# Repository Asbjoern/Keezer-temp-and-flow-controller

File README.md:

# Keezer temp and flow controller
 Beer fridge controller with stock counting

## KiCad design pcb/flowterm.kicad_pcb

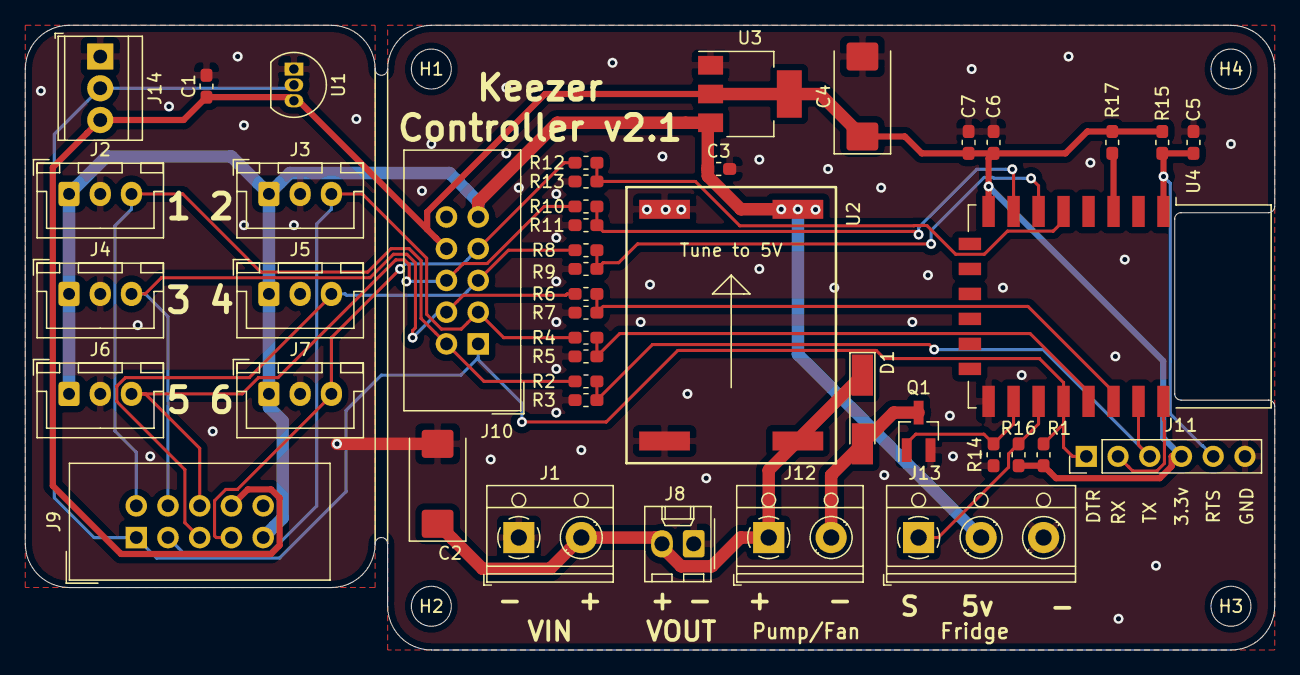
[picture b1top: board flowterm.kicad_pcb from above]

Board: 2 copper layers, 100.0 x 50.0 mm, 48 parts (0 on the bottom side), 23 nets.

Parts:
C1, C5, C7: 100n; C_0603_1608Metric_Pad1.05x0.95mm_HandSolder
C2, C4: 100u; CP_EIA-7343-15_Kemet-W_Pad2.25x2.55mm_HandSolder
C3, C6: 10uF; C_0603_1608Metric_Pad1.05x0.95mm_HandSolder
D1: D_Small_ALT; D_MiniMELF_Handsoldering
H1, H2, H3, H4: MountingHole; MountingHole_3.2mm_M3
J1: Vin; TerminalBlock_RND_205-00012_1x02_P5.00mm_Horizontal
J2: Flow1; JST_XH_B3B-XH-A_1x03_P2.50mm_Vertical
J3: Flow2; JST_XH_B3B-XH-A_1x03_P2.50mm_Vertical
J4: Flow3; JST_XH_B3B-XH-A_1x03_P2.50mm_Vertical
J5: Flow4; JST_XH_B3B-XH-A_1x03_P2.50mm_Vertical
J6: Flow5; JST_XH_B3B-XH-A_1x03_P2.50mm_Vertical
J7: Flow6; JST_XH_B3B-XH-A_1x03_P2.50mm_Vertical
J8: Vout; Molex_KK-254_AE-6410-02A_1x02_P2.54mm_Vertical
J9: Snapoff outer; IDC-Header_2x05_P2.54mm_Vertical
J10: Snapoff inner; IDC-Header_2x05_P2.54mm_Vertical
J11: Prog; PinHeader_1x06_P2.54mm_Vertical
J12: Cool pump; TerminalBlock_RND_205-00012_1x02_P5.00mm_Horizontal
J13: Fridge; TerminalBlock_RND_205-00013_1x03_P5.00mm_Horizontal
J14: 1W; TerminalBlock_TE_282834-3_1x03_P2.54mm_Horizontal
Q1: SI2302DS_N-FET; SOT-23_Handsoldering
R1: 4k7; R_0603_1608Metric_Pad1.05x0.95mm_HandSolder
R2, R4, R6, R8, R10, R12, R14, R15, R16, R17: 10k; R_0603_1608Metric_Pad1.05x0.95mm_HandSolder
R3, R5, R7, R9, R11, R13: 20k; R_0603_1608Metric_Pad1.05x0.95mm_HandSolder
U1: DS18B20; TO-92_Inline
U2: MP1584 module; MP1584module
U3: AMS1117-3.3; SOT-223-3_TabPin2
U4: ESP-12F; ESP-12E

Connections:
+3V3: C1.1, C4.1, C6.1, C7.1, J9.8, J10.8, J11.4, J14.3, R1.2, R15.2, R16.2, R17.2, U1.3, U3.2, U4.8
+5V: C3.1, J2.1, J3.1, J4.1, J5.1, J6.1, J7.1, J9.9, J10.9, J13.2, U2.2, U3.3
/EN: R17.1, U4.3
/FL2: R4.2, R5.1, U4.19
/FL3: R6.2, R7.1, U4.20
/FL4: R8.2, R9.1, U4.6
/FL5: R10.2, R11.1, U4.7
/FL6: R12.2, R13.1, U4.5
/GPIO0_1W: J9.1, J10.1, J11.1, J14.2, R1.1, U1.2, U4.18
/GPIO2_FRIDGE: J13.1, R16.1, U4.17
/GPIO15_PUMP: Q1.1, R14.1, U4.16
/RX_FL1: J11.3, R2.2, R3.1, U4.21
/TX: J11.2, U4.22
/~RST: C5.2, J11.5, R15.1, U4.1
GND: C1.2, C2.2, C3.2, C4.2, C5.1, C6.2, C7.2, J1.1, J2.2, J3.2, J4.2, J5.2, J6.2, J7.2, J8.1, J9.10, J10.10, J11.6, J13.3, J14.1, Q1.2, R3.2, R5.2, R7.2, R9.2, R11.2, R13.2, R14.2, U1.1, U2.1, U3.1, U4.15
unnamed: D1.2, J12.2, Q1.3
unnamed: J2.3, J9.2, J10.2, R2.1
unnamed: J3.3, J9.3, J10.3, R4.1
unnamed: J4.3, J9.4, J10.4, R6.1
unnamed: J5.3, J9.5, J10.5, R8.1
unnamed: J6.3, J9.6, J10.6, R10.1
unnamed: J7.3, J9.7, J10.7, R12.1
VCC: C2.1, D1.1, J1.2, J8.2, J12.1, U2.3

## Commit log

2020-02-26 Inital schematic
2020-02-26 Added PCB layout
2020-05-12 Code added
2020-05-12 PCB: fix silkscreen
2020-05-12 Added beer meta data handling
2020-05-24 fix low memory crash
